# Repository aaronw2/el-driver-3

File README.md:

# el-driver-3
EL Wire Driver using Microchip MIC4832
This is a test board for driving EL wire and panels.
Remove trim pot and JP1 for final version.

Copyright (C) 2021 Aaron Williams

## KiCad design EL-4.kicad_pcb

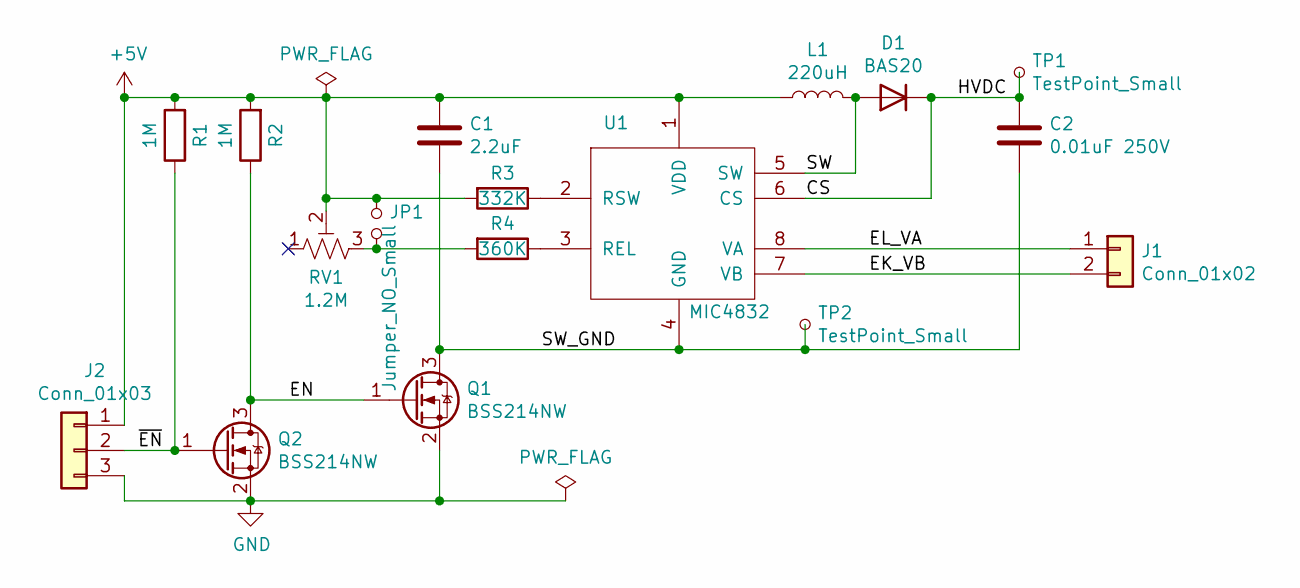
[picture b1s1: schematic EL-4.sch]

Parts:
C1: 2.2uF; C_0603_1608Metric
C2: 0.01uF 250V; C_1206_3216Metric; MPN C1206C103JAGACAUTO
D1: BAS20; SOT-23
J1: Conn_01x02; JST_XH_B2B-XH-A_1x02_P2.50mm_Vertical
J2: Conn_01x03; JST_XH_B3B-XH-A_1x03_P2.50mm_Vertical
JP1: Jumper_NO_Small; SolderJumper-2_P1.3mm_Open_RoundedPad1.0x1.5mm
L1: 220uH; L_Bourns_SRN8040TA
Q1, Q2: BSS214NW; SOT-323_SC-70
R1, R2: 1M; R_0603_1608Metric
R3: 332K; R_0603_1608Metric
R4: 360K; R_0603_1608Metric; MPN RC0603FR-07360KL
RV1: 1.2M; Potentiometer_Bourns_3296W_Vertical; MPN 3296W-1-125LF
TP1, TP2: TestPoint_Small; TestPoint_Pad_D1.0mm
U1: MIC4832; DFN-8-1EP_3x3mm_P0.5mm_EP1.66x2.38mm; MPN MIC4832YMM

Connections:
+5V: C1.1, J2.1, JP1.1, L1.1, R1.2, R2.2, R3.2, RV1.2, U1.1 (VDD)
/CS: C2.1, D1.3 (K), TP1.1, U1.6 (CS)
/EK_VB: J1.2, U1.7 (VB)
/EL_VA: J1.1, U1.8 (VA)
/EN: Q1.1 (G), Q2.3 (D), R2.1
/SW: D1.1 (A), L1.2, U1.5 (SW)
/SW_GND: C1.2, C2.2, Q1.3 (D), TP2.1, U1.4 (GND)
/~EN: J2.2, Q2.1 (G), R1.1
GND: J2.3, Q1.2 (S), Q2.2 (S)
unnamed: JP1.2, R4.2, RV1.3
unnamed: R3.1, U1.2 (RSW)
unnamed: R4.1, U1.3 (REL)

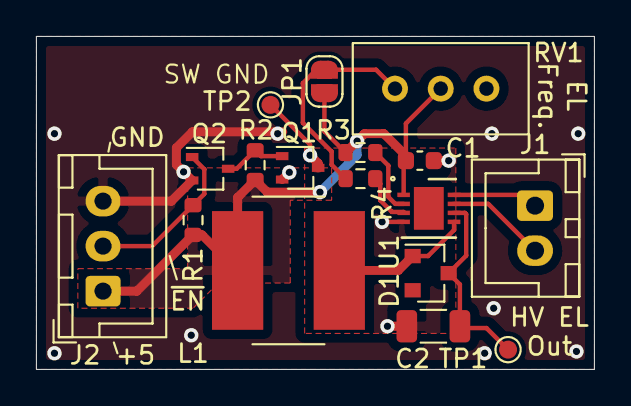
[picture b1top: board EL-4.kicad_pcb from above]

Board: 2 copper layers, 31.0 x 18.5 mm, 17 parts (0 on the bottom side), 12 nets.

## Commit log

2021-01-02 Initial checkin of version 0.9.
2021-01-02 Version 1.0.
    Changed enable method to pull RSW R3 to ground.
    Changed R3, R4, R5 and C2 for 100Hz operation for 3 square inches.
    Added input filter cap.
    Also added BOM.

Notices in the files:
EL-4.kicad_pcb:
Copyright © 2021
